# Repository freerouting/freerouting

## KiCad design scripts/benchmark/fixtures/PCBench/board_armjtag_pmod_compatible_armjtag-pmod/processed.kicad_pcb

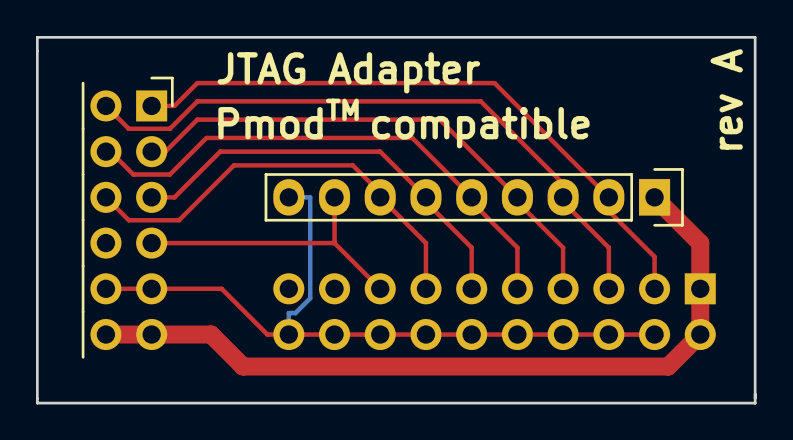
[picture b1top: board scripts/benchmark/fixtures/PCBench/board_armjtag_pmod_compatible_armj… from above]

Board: 2 copper layers, 39.9 x 20.3 mm, 3 parts (1 on the bottom side), 9 nets.

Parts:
P1: CONN_02X06; Socket_Strip_Angled_2x06
P2: CONN_02X10; Socket_Strip_Straight_2x10
P3: CONN_01X09; Socket_Strip_Straight_1x09

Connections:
+3V3: P1.11, P1.12, P2.1, P2.2, P3.1
GND: P1.9, P1.10, P2.4, P2.6, P2.8, P2.10, P2.12, P2.14, P2.16, P2.18, P2.20, P3.9
TRTCK: P1.5, P2.11, P3.6
TSRST_N: P1.7, P2.15, P3.8
TTCK: P1.4, P2.9, P3.5
TTDI: P1.2, P2.5, P3.3
TTDO: P1.6, P2.13, P3.7
TTMS: P1.3, P2.7, P3.4
TTRST_N: P1.1, P2.3, P3.2

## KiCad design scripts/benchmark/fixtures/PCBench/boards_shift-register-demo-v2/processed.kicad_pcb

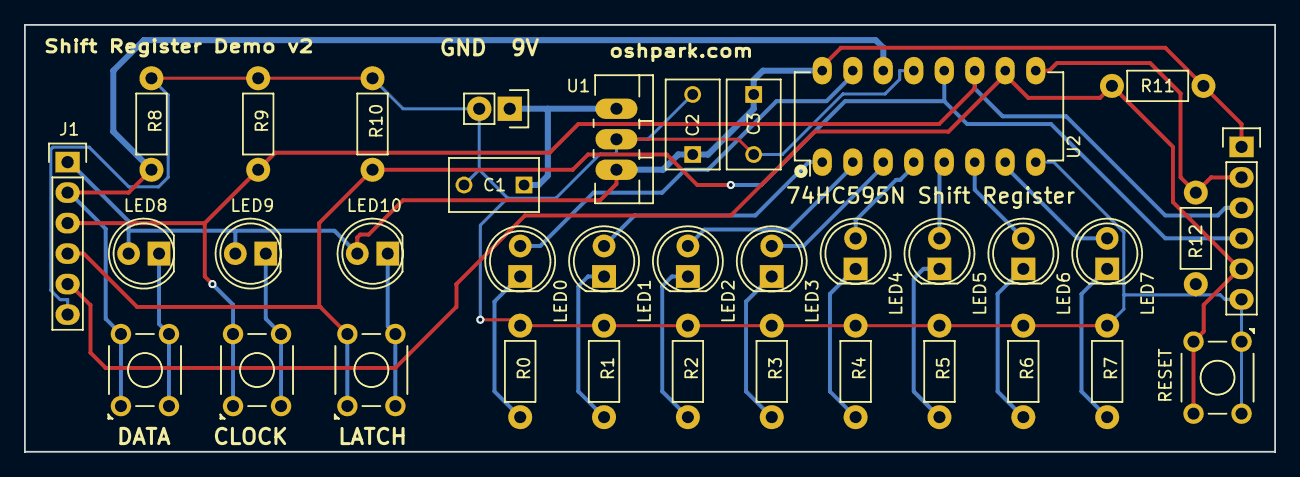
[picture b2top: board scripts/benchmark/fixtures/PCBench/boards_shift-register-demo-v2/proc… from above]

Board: 2 copper layers, 104.1 x 35.6 mm, 36 parts (0 on the bottom side), 27 nets.

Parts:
C1: 330nF; CAP-DISC-D7.5MM-P5MM
C2, C3: 100nF; CAP-DISC-D7.5MM-P5MM
J1: CONN_01x06; CONN-HEADER-STRAIGHT-P2.54MM-1x06
J2: VIN; CONN-ONSHORE-SCREW-GREEN-2PIN-TH
J3: CONN-1X06; CONN-HEADER-STRAIGHT-P2.54MM-1x06
LED0, LED1, LED2, LED3, LED4, LED5, LED6, LED7: RED; LED-D5MM-2PIN
LED8, LED9, LED10: GREEN; LED-D5MM-2PIN
R0, R1, R2, R3, R4, R5, R6, R7: 150; RES-CARBONFILM-7MM
R8, R9, R10, R11, R12: 1K; RES-CARBONFILM-7MM
SW1: DATA; SWITCH-OMRON-MOMENTARY-TH-B3F-10XX
SW2: CLOCK; SWITCH-OMRON-MOMENTARY-TH-B3F-10XX
SW3: LATCH; SWITCH-OMRON-MOMENTARY-TH-B3F-10XX
SW4: RESET; SWITCH-OMRON-MOMENTARY-TH-B3F-10XX
U1: NCP7805; TO-220-NEUTRAL123-VERT-LONGPADS
U2: 74HC595; DIP-16-W7.62MM-LONGPADS

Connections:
+5V: C2.1, C3.1, J1.1, J3.1, LED8.2, LED9.2, LED10.2, R11.1, U1.3, U2.16
+9V: C1.1, J2.1, U1.1
/CLOCK: J1.3, J3.3, R9.1, SW2.1, SW2.2, U2.11
/LATCH: J1.4, J3.4, R10.1, SW3.1, SW3.2, U2.12
/RESET: J1.5, J3.5, R11.2, SW4.3, SW4.4, U2.10
/SERIAL_DATA_IN: J1.2, R8.1, SW1.1, SW1.2, U2.14
/SERIAL_DATA_OUT: J3.2, R12.1, U2.9
GND: C1.2, C2.2, C3.2, J1.6, J2.2, J3.6, R0.2, R1.2, R2.2, R3.2, R4.2, R5.2, R6.2, R7.2, R8.2, R9.2, R10.2, R12.2, SW4.1, SW4.2, U1.2, U2.8, U2.13
unnamed: LED0.1, R0.1
unnamed: LED0.2, U2.15
unnamed: LED1.1, R1.1
unnamed: LED1.2, U2.1
unnamed: LED2.1, R2.1
unnamed: LED2.2, U2.2
unnamed: LED3.1, R3.1
unnamed: LED3.2, U2.3
unnamed: LED4.1, R4.1
unnamed: LED4.2, U2.4
unnamed: LED5.1, R5.1
unnamed: LED5.2, U2.5
unnamed: LED6.1, R6.1
unnamed: LED6.2, U2.6
unnamed: LED7.1, R7.1
unnamed: LED7.2, U2.7
unnamed: LED8.1, SW1.3, SW1.4
unnamed: LED9.1, SW2.3, SW2.4
unnamed: LED10.1, SW3.3, SW3.4

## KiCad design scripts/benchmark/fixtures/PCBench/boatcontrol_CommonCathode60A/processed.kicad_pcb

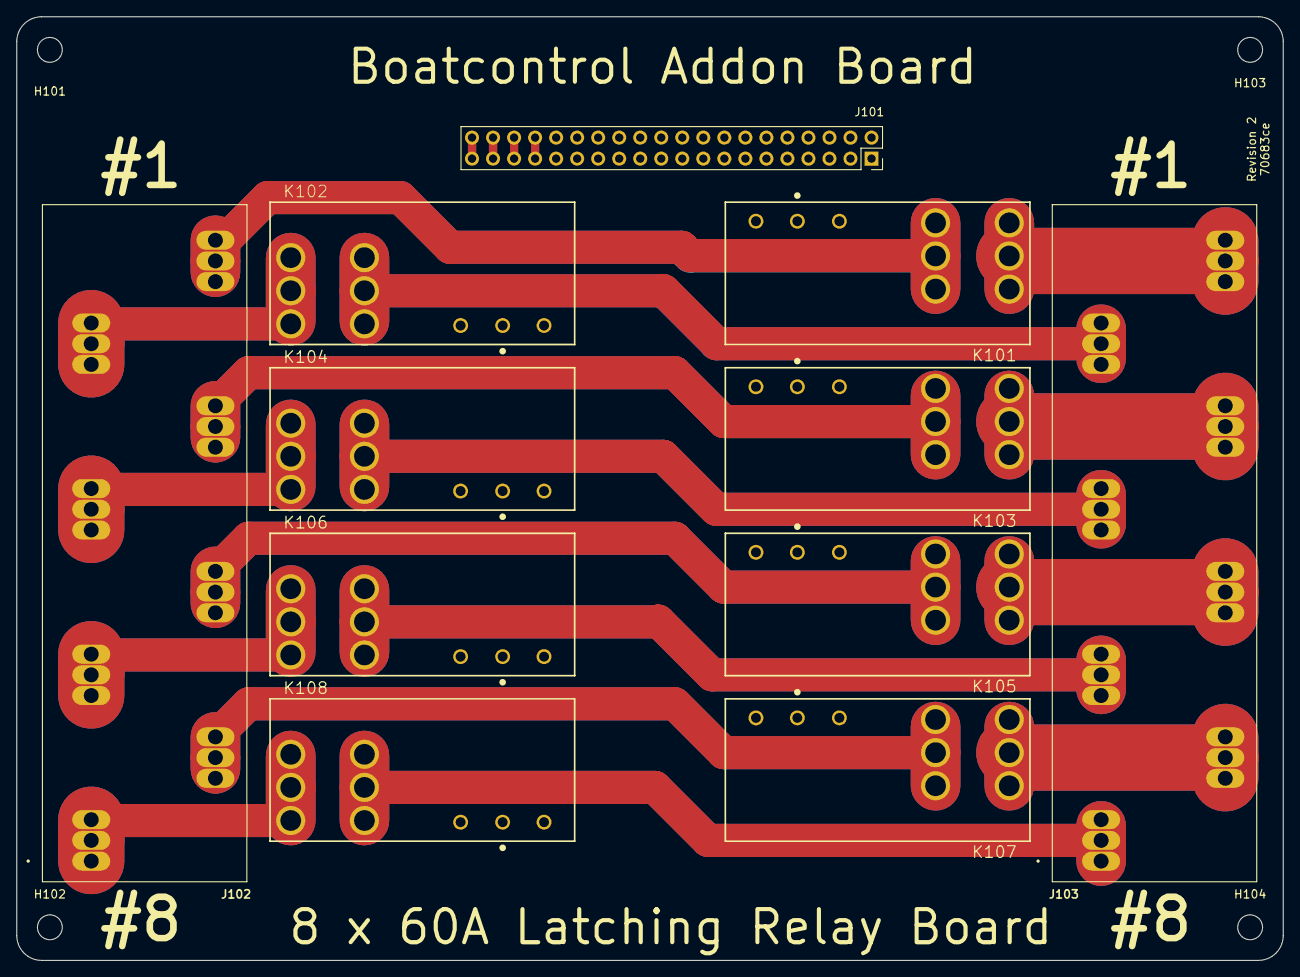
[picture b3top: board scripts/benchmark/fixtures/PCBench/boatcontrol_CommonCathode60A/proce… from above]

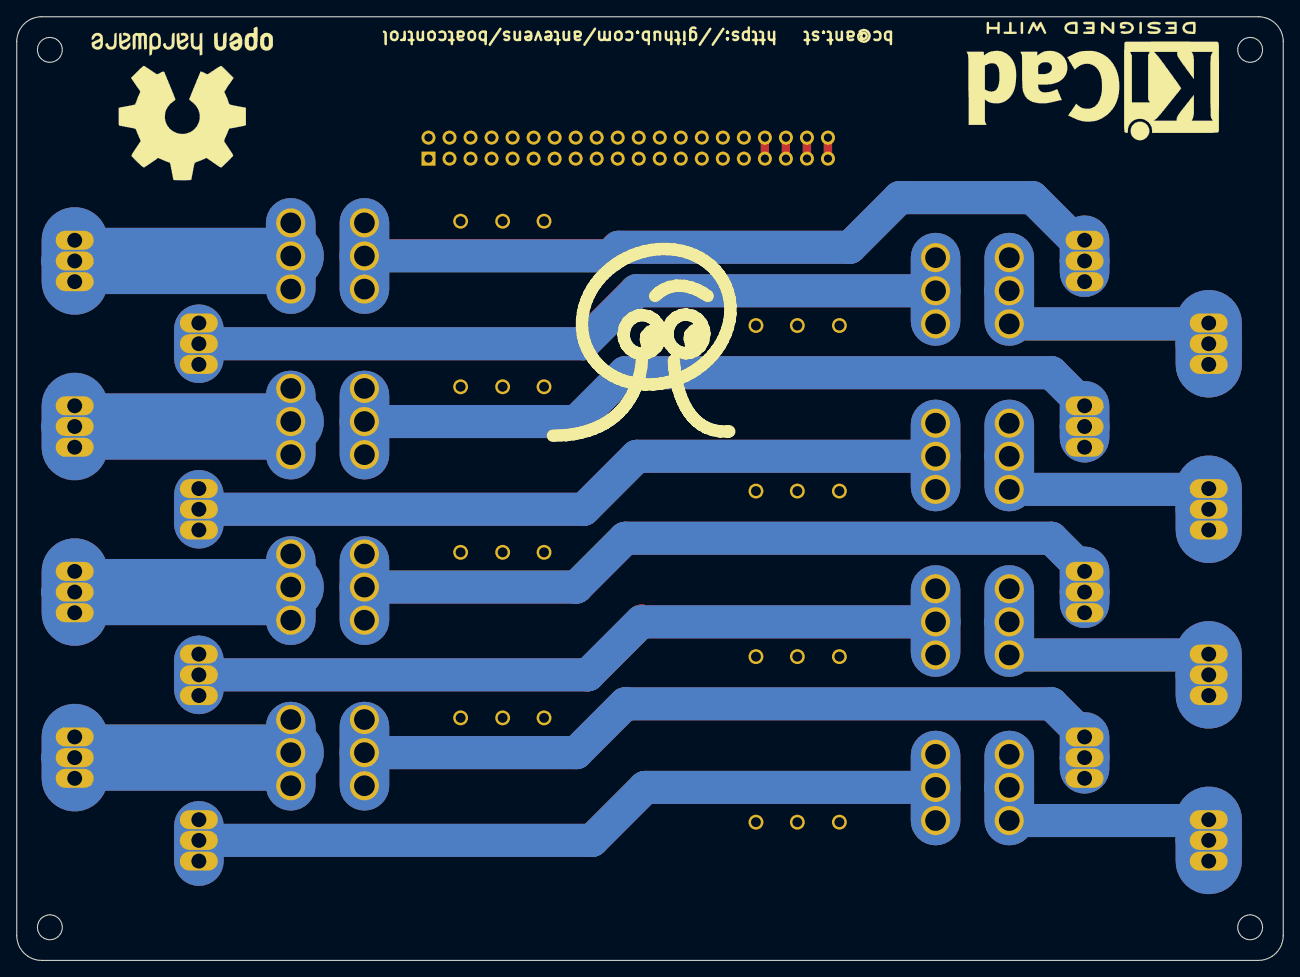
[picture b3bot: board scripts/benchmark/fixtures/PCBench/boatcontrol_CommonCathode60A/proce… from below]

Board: 4 copper layers, 153.0 x 114.0 mm, 18 parts (3 on the bottom side), 33 nets.

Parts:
G102: LOGO_ANT; Ant_Logo_SilkScreen
H101, H102, H103, H104: MountingHole; MountingHole_3mm
J101: Conn_02x20_Odd_Even Header; PinSocket_2x20_P2.54mm_Vertical
J102, J103: TBL008V-1000-08BE; CUI_TBL008V-1000-08BE
K101, K102, K103, K104, K105, K106, K107, K108: EW60-1A3-CL12D04; TE_2071366-2
LOGO101: Logo_Open_Hardware_Large; KiCad-Logo2_12mm_SilkScreen
LOGO102: Logo_Open_Hardware_Large; OSHW-Logo2_24.3x20mm_SilkScreen

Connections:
/K1_COIL_OFF: J101.3, J101.4, K101.A2
/K1_COIL_ON: J101.1, J101.2, K101.A3
/K1_IN: J102.81, J102.82, J102.83, K101.4, K101.5, K101.6
/K1_OUT: J103.81, J103.82, J103.83, K101.1, K101.2, K101.3
/K2_COIL_OFF: J101.7, J101.8, K102.A3
/K2_COIL_ON: J101.5, J101.6, K102.A2
/K2_IN: J102.71, J102.72, J102.73, K102.1, K102.2, K102.3
/K2_OUT: J103.71, J103.72, J103.73, K102.4, K102.5, K102.6
/K3_COIL_OFF: J101.11, J101.12, K103.A2
/K3_COIL_ON: J101.9, J101.10, K103.A3
/K3_IN: J102.61, J102.62, J102.63, K103.4, K103.5, K103.6
/K3_OUT: J103.61, J103.62, J103.63, K103.1, K103.2, K103.3
/K4_COIL_OFF: J101.15, J101.16, K104.A3
/K4_COIL_ON: J101.13, J101.14, K104.A2
/K4_IN: J102.51, J102.52, J102.53, K104.1, K104.2, K104.3
/K4_OUT: J103.51, J103.52, J103.53, K104.4, K104.5, K104.6
/K5_COIL_OFF: J101.19, J101.20, K105.A2
/K5_COIL_ON: J101.17, J101.18, K105.A3
/K5_IN: J102.41, J102.42, J102.43, K105.4, K105.5, K105.6
/K5_OUT: J103.41, J103.42, J103.43, K105.1, K105.2, K105.3
/K6_COIL_OFF: J101.23, J101.24, K106.A3
/K6_COIL_ON: J101.21, J101.22, K106.A2
/K6_IN: J102.31, J102.32, J102.33, K106.1, K106.2, K106.3
/K6_OUT: J103.31, J103.32, J103.33, K106.4, K106.5, K106.6
/K7_COIL_OFF: J101.27, J101.28, K107.A2
/K7_COIL_ON: J101.25, J101.26, K107.A3
/K7_IN: J102.21, J102.22, J102.23, K107.4, K107.5, K107.6
/K7_OUT: J103.21, J103.22, J103.23, K107.1, K107.2, K107.3
/K8_COIL_OFF: J101.31, J101.32, K108.A3
/K8_COIL_ON: J101.29, J101.30, K108.A2
/K8_IN: J102.11, J102.12, J102.13, K108.1, K108.2, K108.3
/K8_OUT: J103.11, J103.12, J103.13, K108.4, K108.5, K108.6
GND: J101.33, J101.34, J101.35, J101.36, J101.37, J101.38, J101.39, J101.40, K101.A1, K102.A1, K103.A1, K104.A1, K105.A1, K106.A1, K107.A1, K108.A1
